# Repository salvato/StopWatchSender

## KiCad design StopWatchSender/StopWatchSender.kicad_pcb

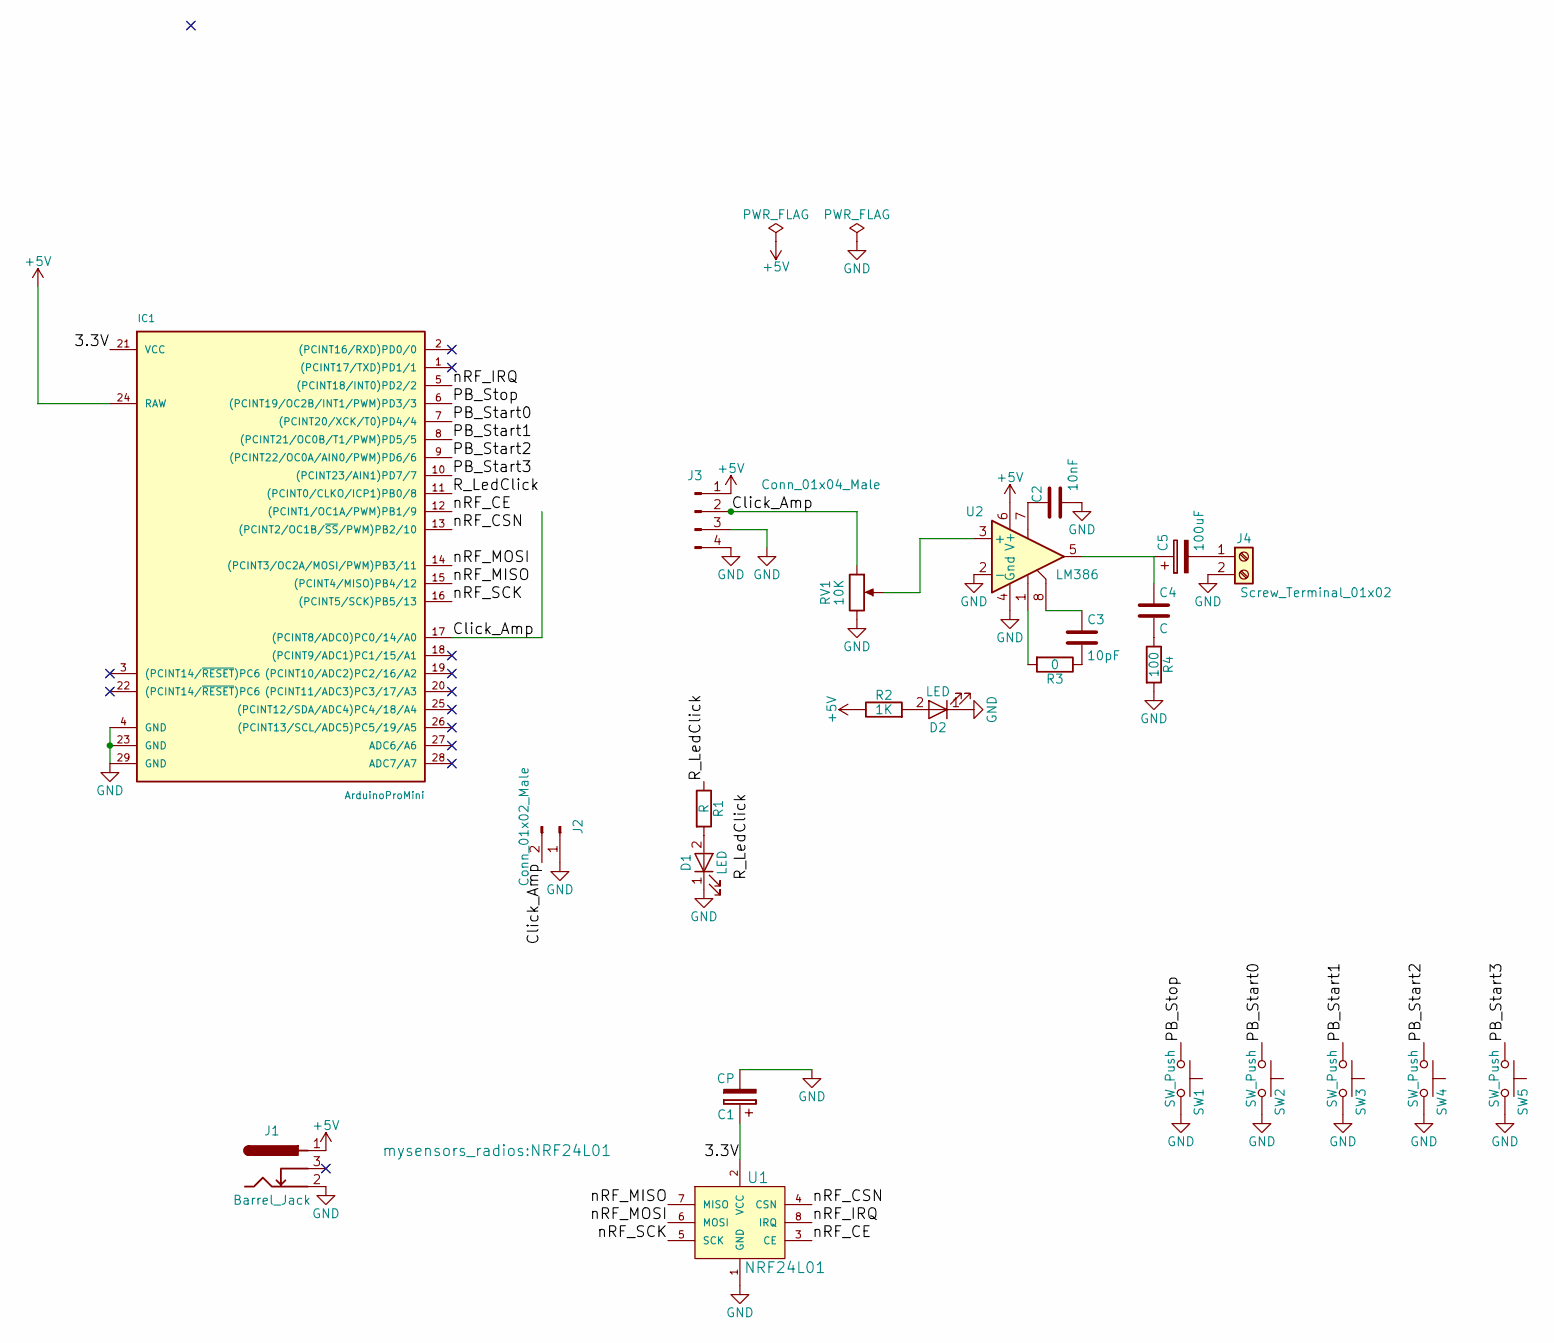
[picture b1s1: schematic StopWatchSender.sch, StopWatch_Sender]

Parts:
C1: CP; CP_Radial_D4.0mm_P1.50mm
C2: 10nF; C_0603
C3: 10pF; C_0603
C4: C; C_0603
C5: 100uF; CP_Radial_D6.3mm_P2.50mm
D1: LED; LED_D4.0mm
D2: LED; LED_0603
IC1: ArduinoProMini; pro_mini
J1: Barrel_Jack; dc_socket-kcswalter
J2: Conn_01x02_Male; Pin_Header_Straight_1x02_Pitch2.54mm
J3: Conn_01x04_Male; Pin_Header_Straight_1x04_Pitch2.54mm
J4: Screw_Terminal_01x02; TerminalBlock2.54mmx2-kcswalter
R1: R; R_Axial_DIN0204_L3.6mm_D1.6mm_P5.08mm_Horizontal
R2: 1K; R_0603
R3: 0; R_0603
R4: 100; R_0603
RV1: 10K; Potentiometer_Trimmer_ACP_CA6v_Horizontal
SW1, SW2, SW3, SW4, SW5: SW_Push; SW_PUSH_6mm_h8mm
U1: NRF24L01
U2: LM386; SOIC-8-N

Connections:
+5V: IC1.24 (RAW), J1.1, J3.1, R2.1, U2.6 (V+)
/3.3V: C1.1, IC1.21 (VCC), U1.2 (VCC)
/Click_Amp: IC1.17 ((PCINT8/ADC0)PC0/14/A0), J2.2, J3.2, RV1.1
/PB_Start0: IC1.7 ((PCINT20/XCK/T0)PD4/4), SW2.1
/PB_Start1: IC1.8 ((PCINT21/OC0B/T1/PWM)PD5/5), SW3.1
/PB_Start2: IC1.9 ((PCINT22/OC0A/AIN0/PWM)PD6/6), SW4.1
/PB_Start3: IC1.10 ((PCINT23/AIN1)PD7/7), SW5.1
/PB_Stop: IC1.6 ((PCINT19/OC2B/INT1/PWM)PD3/3), SW1.1
/R_LedClick: IC1.11 ((PCINT0/CLKO/ICP1)PB0/8), R1.1
/nRF_CE: IC1.12 ((PCINT1/OC1A/PWM)PB1/9), U1.3 (CE)
/nRF_CSN: IC1.13 ((PCINT2/OC1B/~SS~/PWM)PB2/10), U1.4 (CSN)
/nRF_IRQ: IC1.5 ((PCINT18/INT0)PD2/2), U1.8 (IRQ)
/nRF_MISO: IC1.15 ((PCINT4/MISO)PB4/12), U1.7 (MISO)
/nRF_MOSI: IC1.14 ((PCINT3/OC2A/MOSI/PWM)PB3/11), U1.6 (MOSI)
/nRF_SCK: IC1.16 ((PCINT5/SCK)PB5/13), U1.5 (SCK)
GND: C1.2, C2.1, D1.1 (K), D2.1 (K), IC1.4 (GND), IC1.23 (GND), IC1.29 (GND), J1.2, J2.1, J3.3, J3.4, J4.2, R4.2, RV1.3, SW1.2, SW2.2, SW3.2, SW4.2, SW5.2, U1.1 (GND), U2.2 (-), U2.4 (Gnd)
unnamed: C2.2, U2.7
unnamed: C3.1, U2.8
unnamed: C3.2, R3.1
unnamed: C4.1, C5.1, U2.5
unnamed: C4.2, R4.1
unnamed: C5.2, J4.1
unnamed: D1.2 (A), R1.2
unnamed: D2.2 (A), R2.2
unnamed: R3.2, U2.1
unnamed: RV1.2, U2.3 (+)

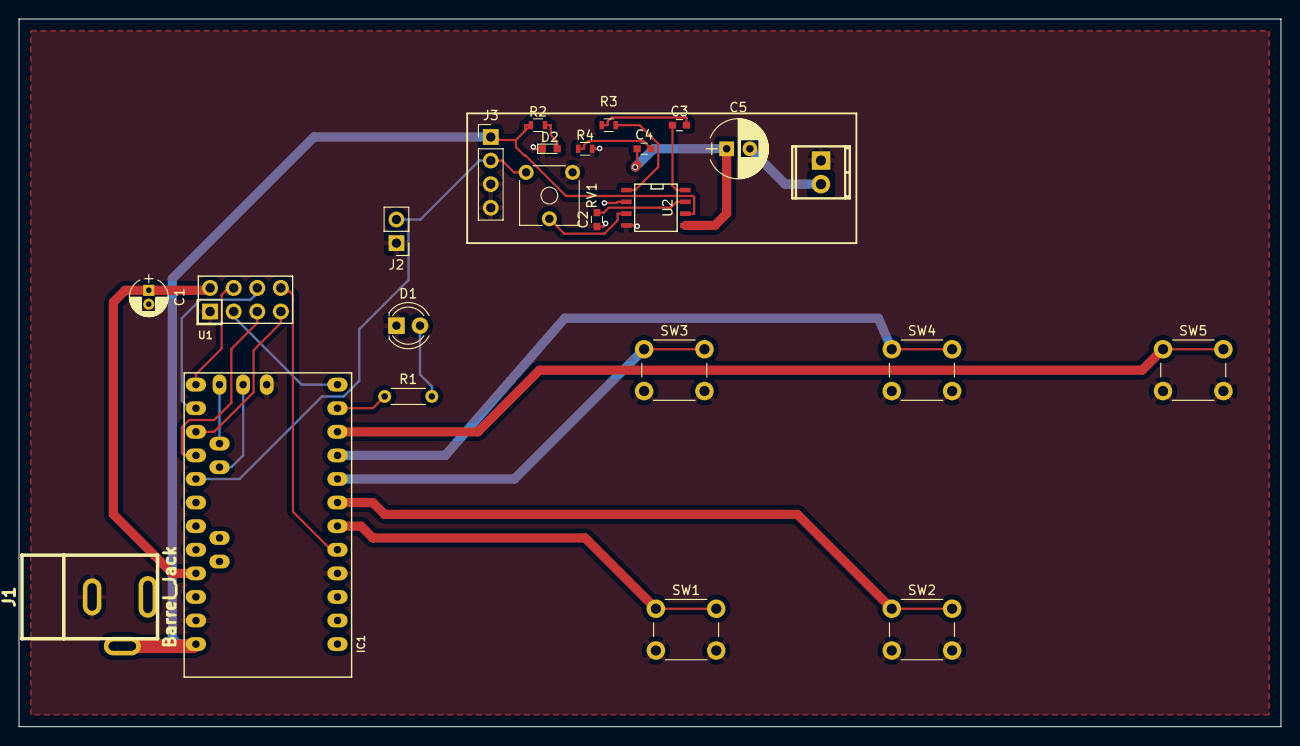
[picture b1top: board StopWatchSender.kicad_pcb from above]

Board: 2 copper layers, 135.9 x 76.2 mm, 24 parts (0 on the bottom side), 26 nets.

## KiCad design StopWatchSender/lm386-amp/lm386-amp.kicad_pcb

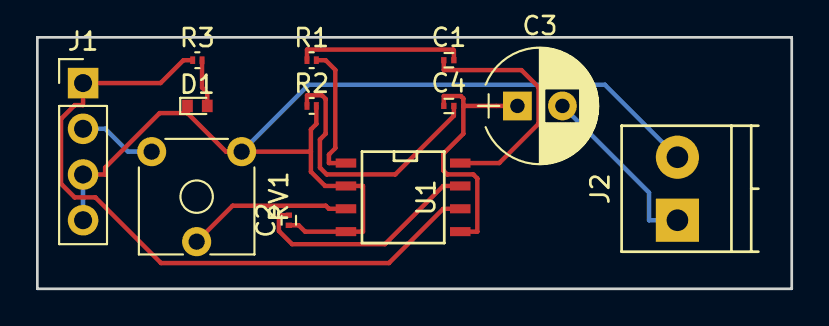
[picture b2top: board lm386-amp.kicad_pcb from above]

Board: 2 copper layers, 41.9 x 14.0 mm, 12 parts (0 on the bottom side), 12 nets.

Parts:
C1: 10pF; C_0201
C2: 10nF; C_0201
C3: 100uF; CP_Radial_D6.3mm_P2.50mm
C4: C; C_0201
D1: LED; LED_0402
J1: Conn_01x04_Male; Pin_Header_Straight_1x04_Pitch2.54mm
J2: Screw_Terminal_01x02; TerminalBlock_Phoenix_PT-3.5mm_2pol
R1: 0; R_0201
R2: 100; R_0201
R3: 1K; R_0201
RV1: 10K; Potentiometer_Trimmer_ACP_CA6v_Horizontal
U1: LM386; SOIC-8-N

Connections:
+5V: J1.1, R3.1, U1.6
GND: C2.1, D1.1, J1.3, J1.4, J2.2, R2.2, RV1.3, U1.2, U1.4
unnamed: C1.1, U1.8
unnamed: C1.2, R1.1
unnamed: C2.2, U1.7
unnamed: C3.1, C4.1, U1.5
unnamed: C3.2, J2.1
unnamed: C4.2, R2.1
unnamed: D1.2, R3.2
unnamed: J1.2, RV1.1
unnamed: R1.2, U1.1
unnamed: RV1.2, U1.3

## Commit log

2017-05-02 aggiunto pulsante 14 secondi
2017-06-12 rimosso l'auto Ack
2018-03-15 articolo
2018-03-17 work in progress on the article
2018-03-21 Aggiunta scatola 3D
2018-03-21 test2
2018-03-21 aggiunti file scatola
2018-03-22 cambiato il top
2018-03-23 inserito link
2018-03-29 aggiunto un file con il possibile setup
2018-03-30 Work in progress on the documentation
2018-04-10 openscad update
2018-04-16 updating document
2018-04-16 Reformatting the top panel
2018-04-17 working on the sketch
2018-04-17 working on the sketch and fritzing
2018-04-17 working on fritzing
2018-04-19 KiCad PCB update
2018-04-20 Working on the electronics
2018-04-20 working
2018-04-21 modified the documentation
2018-05-10 New version
2018-05-15 updated document
2018-05-16 added ntp document
2018-05-18 Changed sketch
2018-05-18 Starting NTP
2018-05-23 updated documents
2018-07-09 updating
2018-07-17 Aggiunto pdf
2018-10-01 document update
